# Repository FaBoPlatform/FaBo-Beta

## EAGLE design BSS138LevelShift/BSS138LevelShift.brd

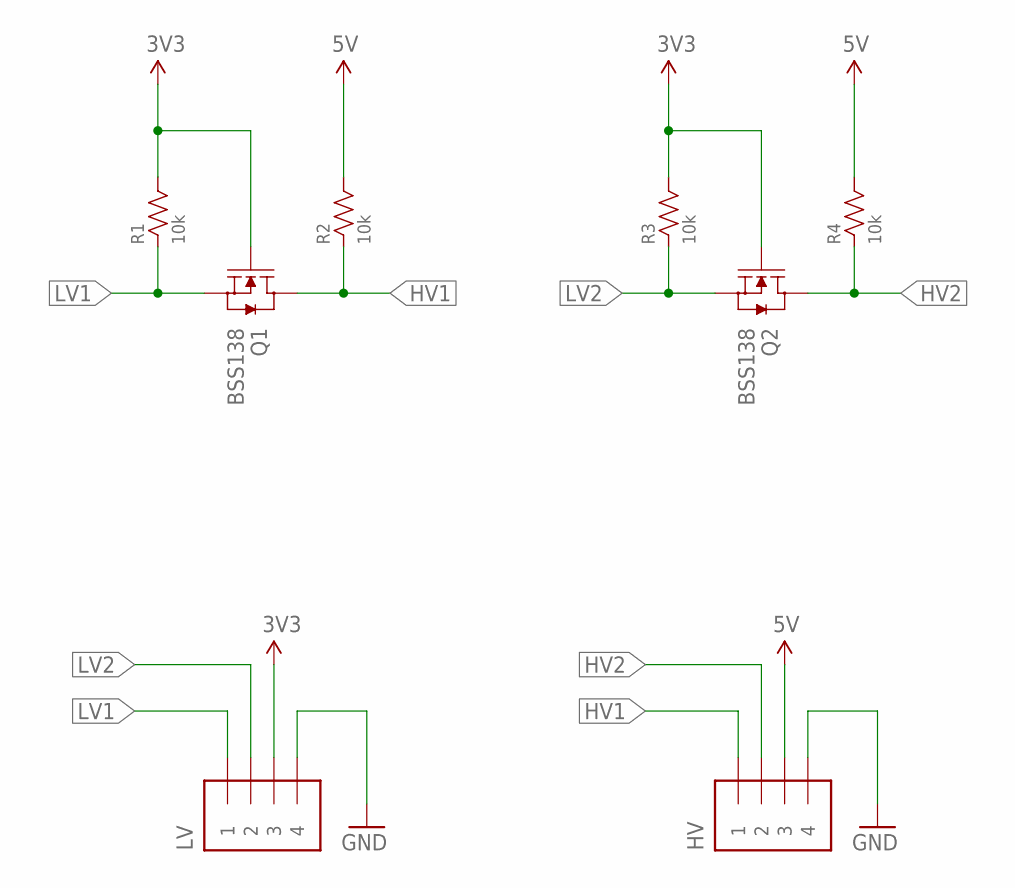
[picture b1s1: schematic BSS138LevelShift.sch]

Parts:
HV: PIN_HEADER_1X4; PIN_1X4_SNEAKY
LV: PIN_HEADER_1X4; PIN_1X4_SNEAKY
Q1, Q2: BSS138; SOT23-3
R1, R2, R3, R4: 10k; 0603

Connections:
3V3: LV.3, Q1.1 (G), Q2.1 (G), R1.2, R3.2
5V: HV.3, R2.2, R4.2
GND: HV.4, LV.4
HV1: HV.1, Q1.3 (D), R2.1
HV2: HV.2, Q2.3 (D), R4.1
LV1: LV.1, Q1.2 (S), R1.1
LV2: LV.2, Q2.2 (S), R3.1

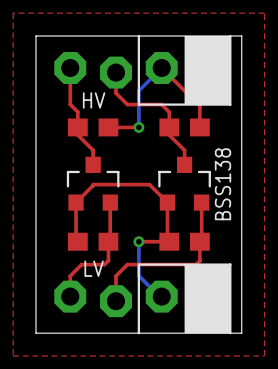
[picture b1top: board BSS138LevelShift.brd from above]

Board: 2 copper layers, 11.4 x 16.5 mm, 8 parts (0 on the bottom side), 7 nets.

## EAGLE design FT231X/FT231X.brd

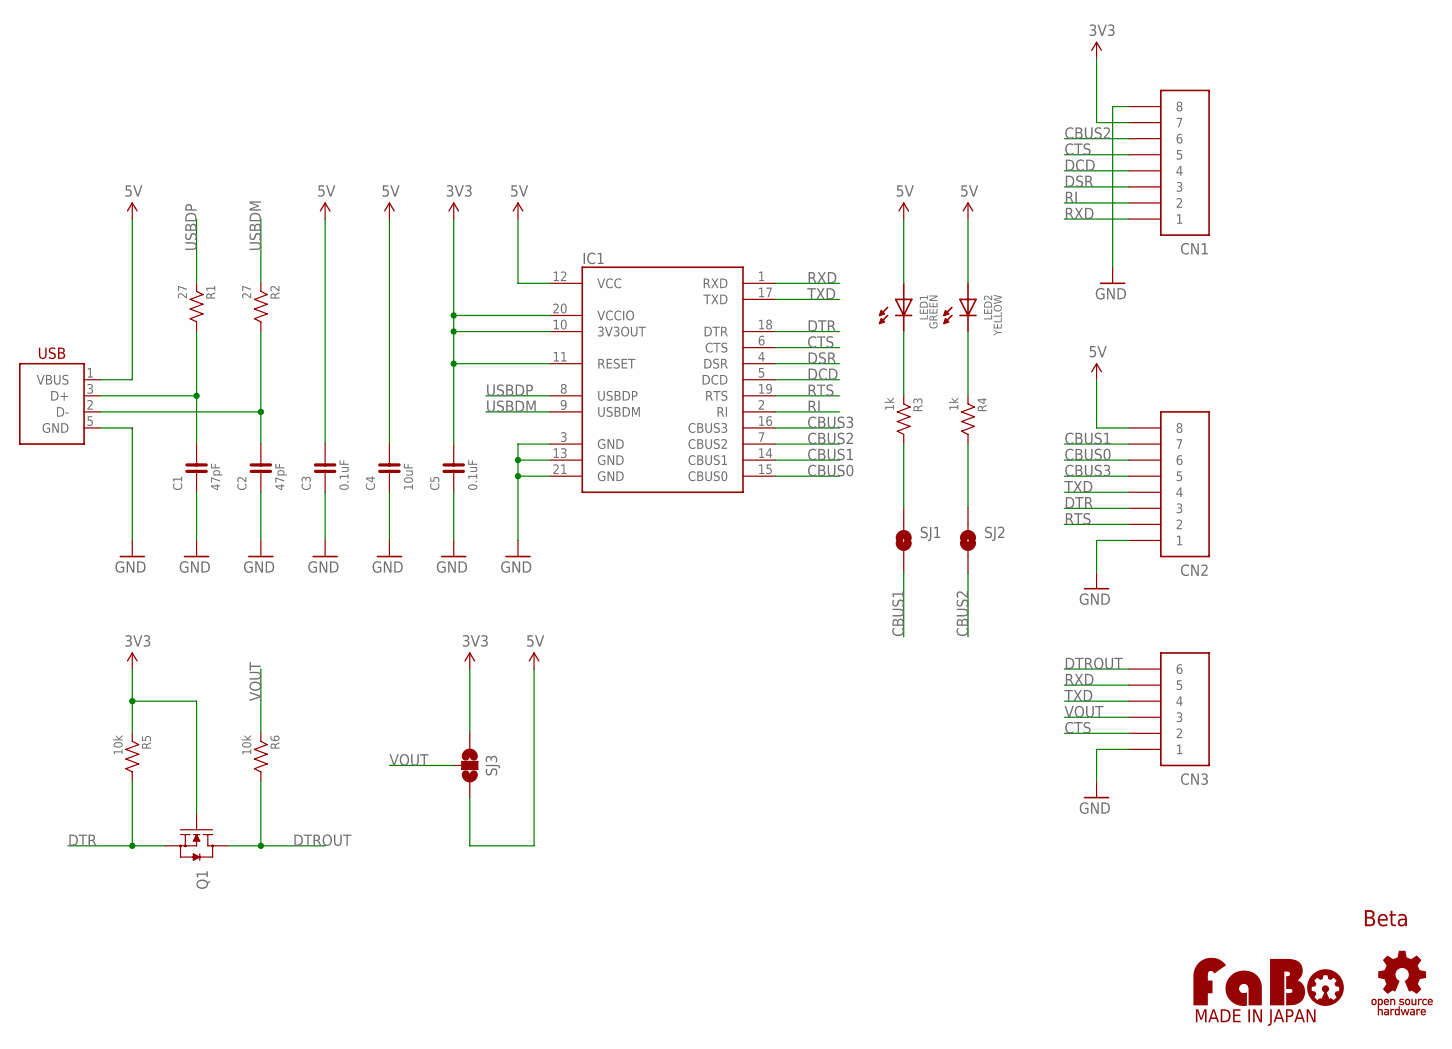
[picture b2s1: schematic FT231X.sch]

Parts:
C1, C2: 47pF; 0603
C3, C5: 0.1uF; 0603
C4: 10uF; 0603
CN1, CN2: PIN_HEADER_1X8-SNEAKY; PIN_1X8_SNEAKY
CN3: PIN_HEADER_1X6-SNEAKY; PIN_1X6_SNEAKY
IC1: FT231XQ; QFN-20
LED1: GREEN; 0603
LED2: YELLOW; 0603
Q1: MOSFET-N-BSS138; SOT23-3
R1, R2: 27; 0603
R3, R4: 1k; 0603
R5, R6: 10k; 0603
SJ1, SJ2: SMD-JUMPER-2_SHORT; SMD-JUMPER-2-SHORT
SJ3: SMD-JUMPER-3_23SHORT; SMD-JUMPER-3-23SHORT
U$2: LOGO_OSHW-T_M_BOTTOM; LOGO_OSHW_T_MS_BOTTOM
U$3: LOGO_FABO-S; LOGO_FABO_S
USB1: USB-MICRO_B_SMT; DX4R005JJ2R1800

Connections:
3V3: C5.2, CN1.7, IC1.10 (3V3OUT), IC1.11 (RESET), IC1.20 (VCCIO), Q1.1 (G), R5.1, SJ3.1
5V: C3.2, C4.2, CN2.8, IC1.12 (VCC), LED1.ANODE, LED2.ANODE, SJ3.3, USB1.1 (VBUS)
CBUS0: CN2.6, IC1.15 (CBUS0)
CBUS1: CN2.7, IC1.14 (CBUS1), SJ1.2
CBUS2: CN1.6, IC1.7 (CBUS2), SJ2.2
CBUS3: CN2.5, IC1.16 (CBUS3)
CTS: CN1.5, CN3.2, IC1.6 (CTS)
DCD: CN1.4, IC1.5 (DCD)
DSR: CN1.3, IC1.4 (DSR)
DTR: CN2.3, IC1.18 (DTR), Q1.2 (S), R5.2
DTROUT: CN3.6, Q1.3 (D), R6.2
GND: C1.1, C2.1, C3.1, C4.1, C5.1, CN1.8, CN2.1, CN3.1, IC1.3 (GND), IC1.13 (GND), IC1.21 (GND), USB1.5 (GND)
unnamed: C2.2, R2.2, USB1.2 (D-)
unnamed: C1.2, R1.2, USB1.3 (D+)
unnamed: LED1.CATHODE, R3.1
unnamed: R3.2, SJ1.1
unnamed: LED2.CATHODE, R4.1
unnamed: R4.2, SJ2.1
RI: CN1.2, IC1.2 (RI)
RTS: CN2.2, IC1.19 (RTS)
RXD: CN1.1, CN3.5, IC1.1 (RXD)
TXD: CN2.4, CN3.4, IC1.17 (TXD)
USBDM: IC1.9 (USBDM), R2.1
USBDP: IC1.8 (USBDP), R1.1
VOUT: CN3.3, R6.1, SJ3.2

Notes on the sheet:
Beta

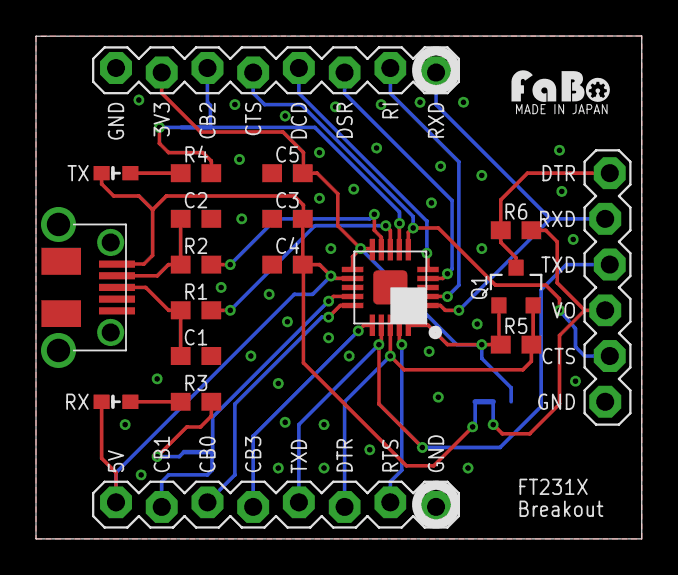
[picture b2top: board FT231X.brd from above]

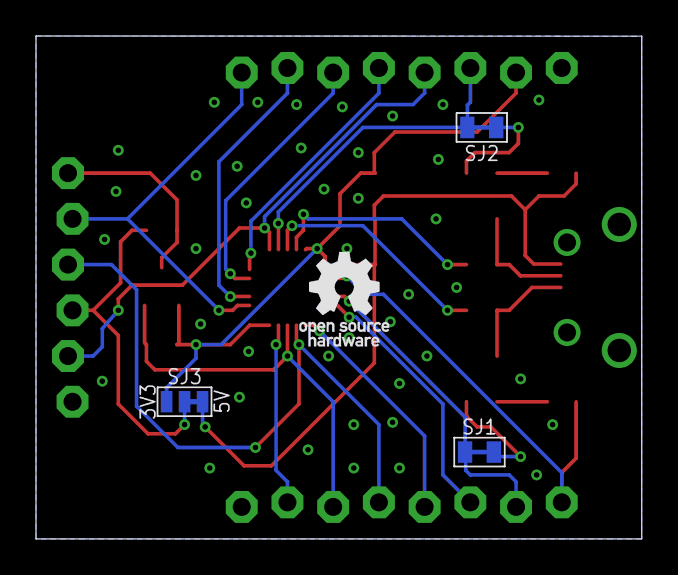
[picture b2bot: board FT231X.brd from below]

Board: 2 copper layers, 33.7 x 27.9 mm, 24 parts (3 on the bottom side), 25 nets.

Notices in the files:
parts and their libraries:
FaBo-etc: Released under the Creative Commons Attribution-ShareAlike 4.0 License
https://creativecommons.org/licenses/by-sa/4.0
FaBo-etc: Released under the Creative Commons
